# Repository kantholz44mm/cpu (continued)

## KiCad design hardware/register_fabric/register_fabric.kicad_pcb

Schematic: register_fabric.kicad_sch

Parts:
C2, C3, C5, C6, C8, C9, C11, C12, C14, C15, C17, C18, C20, C21, C23, C24, C25, C26, C27, C28, C29, C30, C31, C32, C33, C34, C35, C36: 330nF; C_0402_1005Metric; LCSC C77020
C4, C7, C10, C13, C16, C19, C22: 22uF; C_Radial_D5.0mm_H11.0mm_P2.00mm; not fitted
D141, D142, D143, D144, D145, D146, D147, D148, D149, D150, D151, D152, D153, D154, D155, D156, D157, D158, D159, D160, D161, D162, D163, D164, D165, D166, D167, D168, D169, D170, D171, D172, D173, D174, D175, D176, D177, D178, D179, D180, D181, D182, D183, D184, D185, D186, D187, D188, D189, D190, D191, D192, D193, D194, D195, D196, D197, D198, D199, D200, D201, D202: LED; LED_0402_1005Metric; LCSC C965793
H1, H2, H3, H4, H5, H6, H7, H8: MountingHole_Pad; MountingHole_3.2mm_M3_ISO7380_Pad_TopBottom
J2: Conn_02x40_Odd_Even; PinSocket_2x40_P2.54mm_Horizontal; not fitted
J3, J4, J5, J6, J7, J8, J9: Conn_02x16_Odd_Even; PinSocket_2x16_P2.54mm_Horizontal; not fitted
Q109, Q111, Q113, Q115, Q117, Q119, Q121, Q123, Q125, Q127, Q129, Q131, Q133, Q135, Q137, Q139, Q141, Q143, Q145, Q147, Q149, Q151, Q153, Q155, Q157, Q159, Q161, Q163, Q165, Q167, Q169, Q171, Q173, Q175, Q177, Q179, Q181, Q183, Q185, Q187, Q189, Q191, Q193, Q195, Q197, Q199, Q201, Q203, Q205, Q207, Q209, Q211, Q213, Q215, Q217, Q219, Q221, Q223, Q225, Q227, Q229: IRLML6244; SOT-23; LCSC C5123965
Q110, Q112, Q114, Q116, Q118, Q120, Q122, Q124, Q126, Q128, Q130, Q132, Q134, Q136, Q138, Q140, Q142, Q144, Q146, Q148, Q150, Q152, Q154, Q156, Q158, Q160, Q162, Q164, Q166, Q168, Q170, Q172, Q174, Q176, Q178, Q180, Q182, Q184, Q186, Q188, Q190, Q192, Q194, Q196, Q198, Q200, Q202, Q204, Q206, Q208, Q210, Q212, Q214, Q216, Q218, Q220, Q222, Q224, Q226, Q228, Q230: IRLML6402; SOT-23; LCSC C2886430
R1, R2, R3, R4, R5, R6, R7, R8, R9, R10, R11, R12, R13, R14, R15, R16, R21, R22, R23, R24, R25, R26, R27, R28, R29, R30, R31, R32, R33, R34, R35, R36, R37, R38, R39, R40, R41, R45, R46, R47, R48, R49, R50, R51, R52: 100K; R_0402_1005Metric; LCSC C60491
R122, R123, R124, R125, R126, R127, R128, R129, R130, R131, R132, R133, R134, R135, R136, R137, R138, R139, R140, R141, R142, R143, R144, R145, R146, R147, R148, R149, R150, R151, R152, R153, R154, R155, R156, R157, R158, R159, R160, R161, R162, R163, R164, R165, R166, R167, R168, R169, R170, R171, R172, R173, R174, R175, R176, R177, R178, R179, R180, R181, R182, R183, R184, R185, R186, R187, R188, R189, R190, R191, R192, R193, R194, R195, R196, R197, R198, R199, R200, R201, R202, R203, R204, R205, R206, R207, R208, R209, R210, R211, R212, R213, R214, R215, R216, R217, R218, R219, R220, R221, R222, R223, R224, R225, R226, R227, R228, R229, R230, R231, R232, R233, R234, R235, R236, R237, R238, R239, R240, R241, R242, R243, R244: 1000; R_0402_1005Metric; LCSC C106235
U1, U3, U4, U5, U6, U7, U8, U9, U10, U11, U12, U13, U14, U15, U16, U17: 74HC245; TSSOP-20_4.4x6.5mm_P0.65mm; LCSC C5626
U2, U18: 74HC138; SOIC-16_3.9x9.9mm_P1.27mm; LCSC C5602
U19, U21, U22, U23, U24, U25, U26: 74HC00; SOIC-14_3.9x8.7mm_P1.27mm; LCSC C5586
U20: 74HC238; SOIC-16_3.9x9.9mm_P1.27mm; LCSC C5620
U89, U90: 74LS157; SOIC-16_3.9x9.9mm_P1.27mm; LCSC C6823

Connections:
+5V: C2.1, C3.1, C4.1, C5.1, C6.1, C7.1, C8.1, C9.1, C10.1, C11.1, C12.1, C13.1, C14.1, C15.1, C16.1, C17.1, C18.1, C19.1, C20.1, C21.1, C22.1, C23.1, C24.1, C25.1, C26.1, C27.1, C28.1, C29.1, C30.1, C31.1, C32.1, C33.1, C34.1, C35.1, C36.1, D202.2 (A), J2.71, J2.73, J2.75, J2.77, J3.24, J3.26, J3.28, J3.30, J4.24, J4.26, J4.28, J4.30, J5.24, J5.26, J5.28, J5.30, J6.24, J6.26, J6.28, J6.30, J7.24, J7.26, J7.28, J7.30, J8.24, J8.26, J8.28, J8.30, J9.24, J9.26, J9.28, J9.30, Q110.2 (S), Q112.2 (S), Q114.2 (S), Q116.2 (S), Q118.2 (S), Q120.2 (S), Q122.2 (S), Q124.2 (S), Q126.2 (S), Q128.2 (S), Q130.2 (S), Q132.2 (S), Q134.2 (S), Q136.2 (S), Q138.2 (S), Q140.2 (S), Q142.2 (S), Q144.2 (S), Q146.2 (S), Q148.2 (S), Q150.2 (S), Q152.2 (S), Q154.2 (S), Q156.2 (S), Q158.2 (S), Q160.2 (S), Q162.2 (S), Q164.2 (S), Q166.2 (S), Q168.2 (S), Q170.2 (S), Q172.2 (S), Q174.2 (S), Q176.2 (S), Q178.2 (S), Q180.2 (S), Q182.2 (S), Q184.2 (S), Q186.2 (S), Q188.2 (S), Q190.2 (S), Q192.2 (S), Q194.2 (S), Q196.2 (S), Q198.2 (S), Q200.2 (S), Q202.2 (S), Q204.2 (S), Q206.2 (S), Q208.2 (S), Q210.2 (S), Q212.2 (S), Q214.2 (S), Q216.2 (S), Q218.2 (S), Q220.2 (S), Q222.2 (S), Q224.2 (S), Q226.2 (S), Q228.2 (S), Q230.2 (S), R1.1, R2.1, R3.1, R4.1, R5.1, R6.1, R7.1, R8.1, R9.1, R10.1, R11.1, R12.1, R13.1, R14.1, R15.1, R16.1, R122.2, R123.2, R124.2, R125.2, R126.2, R127.2, R128.2, R129.2, R130.2, R131.2, R132.2, R133.2, R134.2, R135.2, R136.2, R137.2, R138.2, R139.2, R140.2, R141.2, R142.2, R143.2, R144.2, R145.2, R146.2, R147.2, R148.2, R149.2, R150.2, R151.2, R152.2, R153.2, R154.2, R155.2, R156.2, R157.2, R158.2, R159.2, R160.2, R161.2, R162.2, R163.2, R164.2, R208.2, R210.2, R212.2, R214.2, R216.2, R218.2, R220.2, R222.2, R224.2, R226.2, R228.2, R230.2, R232.2, R234.2, R236.2, R238.2, R240.2, R242.2, U1.1 (A->B), U1.20 (VCC), U2.6 (E2), U2.16 (VCC), U3.1 (A->B), U3.20 (VCC), U4.1 (A->B), U4.20 (VCC), U5.1 (A->B), U5.20 (VCC), U6.1 (A->B), U6.20 (VCC), U7.1 (A->B), U7.20 (VCC), U8.1 (A->B), U8.20 (VCC), U9.1 (A->B), U9.20 (VCC), U10.1 (A->B), U10.20 (VCC), U11.1 (A->B), U11.20 (VCC), U12.1 (A->B), U12.20 (VCC), U13.1 (A->B), U13.20 (VCC), U14.1 (A->B), U14.20 (VCC), U15.1 (A->B), U15.20 (VCC), U16.1 (A->B), U16.20 (VCC), U17.1 (A->B), U17.20 (VCC), U18.6 (E2), U18.16 (VCC), U19.14 (VCC), U20.6 (E3), U20.16 (VCC), U21.14 (VCC), U22.14 (VCC), U23.14 (VCC), U24.14 (VCC), U25.14 (VCC), U26.14 (VCC), U89.16 (VCC), U90.16 (VCC)
/!CLR: J2.65, Q229.1 (G), R41.1
/CLK: J2.67, Q227.1 (G), R40.1
/COUT: J2.74, J7.5, U12.4 (A2), U13.4 (A2)
/DI0: J2.3, Q123.1 (G), R28.1
/DI1: J2.5, Q121.1 (G), R27.1
/DI2: J2.7, Q119.1 (G), R26.1
/DI3: J2.9, Q117.1 (G), R25.1
/DI4: J2.11, Q115.1 (G), R24.1
/DI5: J2.13, Q113.1 (G), R23.1
/DI6: J2.15, Q111.1 (G), R22.1
/DI7: J2.17, Q109.1 (G), R21.1
/DII0: D148.2 (A), J3.13, J4.13, J5.13, J6.13, J8.13, J9.13, Q124.3 (D), U89.2 (I0a)
/DII1: D147.2 (A), J3.14, J4.14, J5.14, J6.14, J8.14, J9.14, Q122.3 (D), U89.5 (I0b)
/DII2: D146.2 (A), J3.15, J4.15, J5.15, J6.15, J8.15, J9.15, Q120.3 (D), U89.11 (I0c)
/DII3: D145.2 (A), J3.16, J4.16, J5.16, J6.16, J8.16, J9.16, Q118.3 (D), U89.14 (I0d)
/DII4: D144.2 (A), J3.17, J4.17, J5.17, J6.17, J8.17, J9.17, Q116.3 (D), U90.2 (I0a)
/DII5: D143.2 (A), J3.18, J4.18, J5.18, J6.18, J8.18, J9.18, Q114.3 (D), U90.5 (I0b)
/DII6: D142.2 (A), J3.19, J4.19, J5.19, J6.19, J8.19, J9.19, Q112.3 (D), U90.11 (I0c)
/DII7: D141.2 (A), J3.20, J4.20, J5.20, J6.20, J8.20, J9.20, Q110.3 (D), U90.14 (I0d)
/FI0: J2.4, Q171.1 (G), R52.1
/FI1: J2.6, Q169.1 (G), R51.1
/FI2: J2.8, Q167.1 (G), R50.1
/FI3: J2.10, Q165.1 (G), R49.1
/FI4: J2.12, Q163.1 (G), R48.1
/FI5: J2.14, Q161.1 (G), R47.1
/FI6: J2.16, Q159.1 (G), R46.1
/FI7: J2.18, Q157.1 (G), R45.1
/FII0: D172.2 (A), Q172.3 (D), U89.3 (I1a)
/FII1: D171.2 (A), Q170.3 (D), U89.6 (I1b)
/FII2: D170.2 (A), Q168.3 (D), U89.10 (I1c)
/FII3: D169.2 (A), Q166.3 (D), U89.13 (I1d)
/FII4: D168.2 (A), Q164.3 (D), U90.3 (I1a)
/FII5: D167.2 (A), Q162.3 (D), U90.6 (I1b)
/FII6: D166.2 (A), Q160.3 (D), U90.10 (I1c)
/FII7: D165.2 (A), Q158.3 (D), U90.13 (I1d)
/FWEN: J2.78, Q225.1 (G), R39.1
/I!CLR: D201.2 (A), J3.29, J4.29, J5.29, J6.29, J7.29, J8.29, J9.29, Q230.3 (D)
/ICLK: D200.2 (A), J3.25, J4.25, J5.25, J6.25, J7.25, J8.25, J9.25, Q228.3 (D)
/IFWEN: D199.2 (A), Q226.3 (D), U24.9, U24.10, U89.1 (S), U90.1 (S)
/IRWEN: D198.2 (A), Q224.3 (D), U19.1, U21.1, U22.1, U23.1, U24.1, U25.1, U26.1
/R00: D156.2 (A), J2.21, Q140.3 (D)
/R01: D155.2 (A), J2.23, Q138.3 (D)
/R02: D154.2 (A), J2.25, Q136.3 (D)
/R03: D153.2 (A), J2.27, Q134.3 (D)
/R04: D152.2 (A), J2.29, Q132.3 (D)
/R05: D151.2 (A), J2.31, Q130.3 (D)
/R06: D150.2 (A), J2.33, Q128.3 (D)
/R07: D149.2 (A), J2.35, Q126.3 (D)
/R10: D164.2 (A), J2.22, Q156.3 (D)
/R11: D163.2 (A), J2.24, Q154.3 (D)
/R12: D162.2 (A), J2.26, Q152.3 (D)
/R13: D161.2 (A), J2.28, Q150.3 (D)
/R14: D160.2 (A), J2.30, Q148.3 (D)
/R15: D159.2 (A), J2.32, Q146.3 (D)
/R16: D158.2 (A), J2.34, Q144.3 (D)
/R17: D157.2 (A), J2.36, Q142.3 (D)
/RA0: D188.2 (A), J2.39, Q204.3 (D)
/RA1: D187.2 (A), J2.41, Q202.3 (D)
/RA2: D186.2 (A), J2.43, Q200.3 (D)
/RA3: D185.2 (A), J2.45, Q198.3 (D)
/RA4: D184.2 (A), J2.47, Q196.3 (D)
/RA5: D183.2 (A), J2.49, Q194.3 (D)
/RA6: D182.2 (A), J2.51, Q192.3 (D)
/RA7: D181.2 (A), J2.53, Q190.3 (D)
/RA8: D180.2 (A), J2.40, Q188.3 (D)
/RA9: D179.2 (A), J2.42, Q186.3 (D)
/RA10: D178.2 (A), J2.44, Q184.3 (D)
/RA11: D177.2 (A), J2.46, Q182.3 (D)
/RA12: D176.2 (A), J2.48, Q180.3 (D)
/RA13: D175.2 (A), J2.50, Q178.3 (D)
/RA14: D174.2 (A), J2.52, Q176.3 (D)
/RA15: D173.2 (A), J2.54, Q174.3 (D)
/RAI0: J8.3, Q203.1 (G), U14.2 (A0), U15.2 (A0)
/RAI1: J8.4, Q201.1 (G), U14.3 (A1), U15.3 (A1)
/RAI2: J8.5, Q199.1 (G), U14.4 (A2), U15.4 (A2)
/RAI3: J8.6, Q197.1 (G), U14.5 (A3), U15.5 (A3)
/RAI4: J8.7, Q195.1 (G), U14.6 (A4), U15.6 (A4)
/RAI5: J8.8, Q193.1 (G), U14.7 (A5), U15.7 (A5)
/RAI6: J8.9, Q191.1 (G), U14.8 (A6), U15.8 (A6)
/RAI7: J8.10, Q189.1 (G), U14.9 (A7), U15.9 (A7)
/RAI8: J9.3, Q187.1 (G), U16.2 (A0), U17.2 (A0)
/RAI9: J9.4, Q185.1 (G), U16.3 (A1), U17.3 (A1)
/RAI10: J9.5, Q183.1 (G), U16.4 (A2), U17.4 (A2)
/RAI11: J9.6, Q181.1 (G), U16.5 (A3), U17.5 (A3)
/RAI12: J9.7, Q179.1 (G), U16.6 (A4), U17.6 (A4)
/RAI13: J9.8, Q177.1 (G), U16.7 (A5), U17.7 (A5)
/RAI14: J9.9, Q175.1 (G), U16.8 (A6), U17.8 (A6)
/RAI15: J9.10, Q173.1 (G), U16.9 (A7), U17.9 (A7)
/RI00: Q139.1 (G), U1.18 (B0), U4.18 (B0), U6.18 (B0), U8.18 (B0), U10.18 (B0), U12.18 (B0), U14.18 (B0), U16.18 (B0)
/RI01: Q137.1 (G), U1.17 (B1), U4.17 (B1), U6.17 (B1), U8.17 (B1), U10.17 (B1), U12.17 (B1), U14.17 (B1), U16.17 (B1)
/RI02: Q135.1 (G), U1.16 (B2), U4.16 (B2), U6.16 (B2), U8.16 (B2), U10.16 (B2), U12.16 (B2), U14.16 (B2), U16.16 (B2)
/RI03: Q133.1 (G), U1.15 (B3), U4.15 (B3), U6.15 (B3), U8.15 (B3), U10.15 (B3), U12.15 (B3), U14.15 (B3), U16.15 (B3)
/RI04: Q131.1 (G), U1.14 (B4), U4.14 (B4), U6.14 (B4), U8.14 (B4), U10.14 (B4), U12.14 (B4), U14.14 (B4), U16.14 (B4)
/RI05: Q129.1 (G), U1.13 (B5), U4.13 (B5), U6.13 (B5), U8.13 (B5), U10.13 (B5), U12.13 (B5), U14.13 (B5), U16.13 (B5)
/RI06: Q127.1 (G), U1.12 (B6), U4.12 (B6), U6.12 (B6), U8.12 (B6), U10.12 (B6), U12.12 (B6), U14.12 (B6), U16.12 (B6)
/RI07: Q125.1 (G), U1.11 (B7), U4.11 (B7), U6.11 (B7), U8.11 (B7), U10.11 (B7), U12.11 (B7), U14.11 (B7), U16.11 (B7)
/RI10: Q155.1 (G), U3.18 (B0), U5.18 (B0), U7.18 (B0), U9.18 (B0), U11.18 (B0), U13.18 (B0), U15.18 (B0), U17.18 (B0)
/RI11: Q153.1 (G), U3.17 (B1), U5.17 (B1), U7.17 (B1), U9.17 (B1), U11.17 (B1), U13.17 (B1), U15.17 (B1), U17.17 (B1)
/RI12: Q151.1 (G), U3.16 (B2), U5.16 (B2), U7.16 (B2), U9.16 (B2), U11.16 (B2), U13.16 (B2), U15.16 (B2), U17.16 (B2)
/RI13: Q149.1 (G), U3.15 (B3), U5.15 (B3), U7.15 (B3), U9.15 (B3), U11.15 (B3), U13.15 (B3), U15.15 (B3), U17.15 (B3)
/RI14: Q147.1 (G), U3.14 (B4), U5.14 (B4), U7.14 (B4), U9.14 (B4), U11.14 (B4), U13.14 (B4), U15.14 (B4), U17.14 (B4)
/RI15: Q145.1 (G), U3.13 (B5), U5.13 (B5), U7.13 (B5), U9.13 (B5), U11.13 (B5), U13.13 (B5), U15.13 (B5), U17.13 (B5)
/RI16: Q143.1 (G), U3.12 (B6), U5.12 (B6), U7.12 (B6), U9.12 (B6), U11.12 (B6), U13.12 (B6), U15.12 (B6), U17.12 (B6)
/RI17: Q141.1 (G), U3.11 (B7), U5.11 (B7), U7.11 (B7), U9.11 (B7), U11.11 (B7), U13.11 (B7), U15.11 (B7), U17.11 (B7)
/RS00: J2.58, Q209.1 (G), R31.1
/RS01: J2.60, Q207.1 (G), R30.1
/RS02: J2.62, Q205.1 (G), R29.1
/RS10: J2.57, Q215.1 (G), R34.1
/RS11: J2.59, Q213.1 (G), R33.1
/RS12: J2.61, Q211.1 (G), R32.1
/RSI00: D191.2 (A), Q210.3 (D), U2.1 (A0)
/RSI01: D190.2 (A), Q208.3 (D), U2.2 (A1)
/RSI02: D189.2 (A), Q206.3 (D), U2.3 (A2)
/RSI10: D194.2 (A), Q216.3 (D), U18.1 (A0)
/RSI11: D193.2 (A), Q214.3 (D), U18.2 (A1)
/RSI12: D192.2 (A), Q212.3 (D), U18.3 (A2)
/RWEN: J2.76, Q223.1 (G), R38.1
/WS0: J2.66, Q221.1 (G), R37.1
/WS1: J2.68, Q219.1 (G), R36.1
/WS2: J2.70, Q217.1 (G), R35.1
/WSI0: D197.2 (A), Q222.3 (D), U20.1 (A0)
/WSI1: D196.2 (A), Q220.3 (D), U20.2 (A1)
/WSI2: D195.2 (A), Q218.3 (D), U20.3 (A2)
GND: C2.2, C3.2, C4.2, C5.2, C6.2, C7.2, C8.2, C9.2, C10.2, C11.2, C12.2, C13.2, C14.2, C15.2, C16.2, C17.2, C18.2, C19.2, C20.2, C21.2, C22.2, C23.2, C24.2, C25.2, C26.2, C27.2, C28.2, C29.2, C30.2, C31.2, C32.2, C33.2, C34.2, C35.2, C36.2, H1.1, H2.1, H3.1, H4.1, H5.1, H6.1, H7.1, H8.1, J2.1, J2.2, J2.19, J2.20, J2.37, J2.38, J2.55, J2.56, J2.63, J2.64, J2.69, J2.72, J2.79, J2.80, J3.1, J3.2, J3.11, J3.12, J3.21, J3.22, J3.23, J3.31, J3.32, J4.1, J4.2, J4.11, J4.12, J4.21, J4.22, J4.23, J4.31, J4.32, J5.1, J5.2, J5.11, J5.12, J5.21, J5.22, J5.23, J5.31, J5.32, J6.1, J6.2, J6.11, J6.12, J6.21, J6.22, J6.23, J6.31, J6.32, J7.1, J7.2, J7.11, J7.12, J7.21, J7.22, J7.23, J7.31, J7.32, J8.1, J8.2, J8.11, J8.12, J8.21, J8.22, J8.23, J8.31, J8.32, J9.1, J9.2, J9.11, J9.12, J9.21, J9.22, J9.23, J9.31, J9.32, Q109.2 (S), Q111.2 (S), Q113.2 (S), Q115.2 (S), Q117.2 (S), Q119.2 (S), Q121.2 (S), Q123.2 (S), Q125.2 (S), Q127.2 (S), Q129.2 (S), Q131.2 (S), Q133.2 (S), Q135.2 (S), Q137.2 (S), Q139.2 (S), Q141.2 (S), Q143.2 (S), Q145.2 (S), Q147.2 (S), Q149.2 (S), Q151.2 (S), Q153.2 (S), Q155.2 (S), Q157.2 (S), Q159.2 (S), Q161.2 (S), Q163.2 (S), Q165.2 (S), Q167.2 (S), Q169.2 (S), Q171.2 (S), Q173.2 (S), Q175.2 (S), Q177.2 (S), Q179.2 (S), Q181.2 (S), Q183.2 (S), Q185.2 (S), Q187.2 (S), Q189.2 (S), Q191.2 (S), Q193.2 (S), Q195.2 (S), Q197.2 (S), Q199.2 (S), Q201.2 (S), Q203.2 (S), Q205.2 (S), Q207.2 (S), Q209.2 (S), Q211.2 (S), Q213.2 (S), Q215.2 (S), Q217.2 (S), Q219.2 (S), Q221.2 (S), Q223.2 (S), Q225.2 (S), Q227.2 (S), Q229.2 (S), R21.2, R22.2, R23.2, R24.2, R25.2, R26.2, R27.2, R28.2, R29.2, R30.2, R31.2, R32.2, R33.2, R34.2, R35.2, R36.2, R37.2, R38.2, R39.2, R40.2, R41.2, R45.2, R46.2, R47.2, R48.2, R49.2, R50.2, R51.2, R52.2, R165.1, R166.1, R167.1, R168.1, R169.1, R170.1, R171.1, R172.1, R173.1, R174.1, R175.1, R176.1, R177.1, R178.1, R179.1, R180.1, R181.1, R182.1, R183.1, R184.1, R185.1, R186.1, R187.1, R188.1, R189.1, R190.1, R191.1, R192.1, R193.1, R194.1, R195.1, R196.1, R197.1, R198.1, R199.1, R200.1, R201.1, R202.1, R203.1, R204.1, R205.1, R206.1, R207.1, R209.1, R211.1, R213.1, R215.1, R217.1, R219.1, R221.1, R223.1, R225.1, R227.1, R229.1, R231.1, R233.1, R235.1, R237.1, R239.1, R241.1, R243.1, R244.1, U1.2 (A0), U1.3 (A1), U1.4 (A2), U1.5 (A3), U1.6 (A4), U1.7 (A5), U1.8 (A6), U1.9 (A7), U1.10 (GND), U2.4 (~E0), U2.5 (~E1), U2.8 (GND), U3.2 (A0), U3.3 (A1), U3.4 (A2), U3.5 (A3), U3.6 (A4), U3.7 (A5), U3.8 (A6), U3.9 (A7), U3.10 (GND), U4.10 (GND), U5.10 (GND), U6.10 (GND), U7.10 (GND), U8.10 (GND), U9.10 (GND), U10.10 (GND), U11.10 (GND), U12.10 (GND), U13.10 (GND), U14.10 (GND), U15.10 (GND), U16.10 (GND), U17.10 (GND), U18.4 (~E0), U18.5 (~E1), U18.8 (GND), U19.7 (GND), U19.9, U19.10, U19.12, U19.13, U20.4 (~E1), U20.5 (~E2), U20.8 (GND), U21.7 (GND), U21.9, U21.10, U21.12, U21.13, U22.7 (GND), U22.9, U22.10, U22.12, U22.13, U23.7 (GND), U23.9, U23.10, U23.12, U23.13, U24.7 (GND), U24.12, U24.13, U25.7 (GND), U25.9, U25.10, U25.12, U25.13, U26.7 (GND), U26.9, U26.10, U26.12, U26.13, U89.8 (GND), U89.15 (E), U90.8 (GND), U90.15 (E)
unnamed: D141.1 (K), R165.2
unnamed: D142.1 (K), R166.2
unnamed: D143.1 (K), R167.2
unnamed: D144.1 (K), R168.2
unnamed: D145.1 (K), R169.2
unnamed: D146.1 (K), R170.2
unnamed: D147.1 (K), R171.2
unnamed: D148.1 (K), R172.2
unnamed: D149.1 (K), R173.2
unnamed: D150.1 (K), R174.2
unnamed: D151.1 (K), R175.2
unnamed: D152.1 (K), R176.2
unnamed: D153.1 (K), R177.2
unnamed: D154.1 (K), R178.2
unnamed: D155.1 (K), R179.2
unnamed: D156.1 (K), R180.2
unnamed: D157.1 (K), R181.2
unnamed: D158.1 (K), R182.2
unnamed: D159.1 (K), R183.2
unnamed: D160.1 (K), R184.2
unnamed: D161.1 (K), R185.2
unnamed: D162.1 (K), R186.2
unnamed: D163.1 (K), R187.2
unnamed: D164.1 (K), R188.2
unnamed: D165.1 (K), R189.2
unnamed: D166.1 (K), R190.2
unnamed: D167.1 (K), R191.2
unnamed: D168.1 (K), R192.2
unnamed: D169.1 (K), R193.2
unnamed: D170.1 (K), R194.2
unnamed: D171.1 (K), R195.2
unnamed: D172.1 (K), R196.2
unnamed: D173.1 (K), R197.2
unnamed: D174.1 (K), R198.2
unnamed: D175.1 (K), R199.2
unnamed: D176.1 (K), R200.2
unnamed: D177.1 (K), R201.2
unnamed: D178.1 (K), R202.2
unnamed: D179.1 (K), R203.2
unnamed: D180.1 (K), R204.2
unnamed: D181.1 (K), R205.2
unnamed: D182.1 (K), R206.2
unnamed: D183.1 (K), R207.2
unnamed: D184.1 (K), R209.2
unnamed: D185.1 (K), R211.2
unnamed: D186.1 (K), R213.2
unnamed: D187.1 (K), R215.2
unnamed: D188.1 (K), R217.2
unnamed: D189.1 (K), R219.2
unnamed: D190.1 (K), R221.2
unnamed: D191.1 (K), R223.2
unnamed: D192.1 (K), R225.2
unnamed: D193.1 (K), R227.2
unnamed: D194.1 (K), R229.2
unnamed: D195.1 (K), R231.2
unnamed: D196.1 (K), R233.2
unnamed: D197.1 (K), R235.2
unnamed: D198.1 (K), R237.2
unnamed: D199.1 (K), R239.2
unnamed: D200.1 (K), R241.2
unnamed: D201.1 (K), R243.2
unnamed: D202.1 (K), R244.2
unnamed: J3.3, U4.2 (A0), U5.2 (A0)
unnamed: J3.4, U4.3 (A1), U5.3 (A1)
unnamed: J3.5, U4.4 (A2), U5.4 (A2)
unnamed: J3.6, U4.5 (A3), U5.5 (A3)
unnamed: J3.7, U4.6 (A4), U5.6 (A4)
unnamed: J3.8, U4.7 (A5), U5.7 (A5)
unnamed: J3.9, U4.8 (A6), U5.8 (A6)
unnamed: J3.10, U4.9 (A7), U5.9 (A7)
unnamed: J3.27, U19.6
unnamed: J4.3, U6.2 (A0), U7.2 (A0)
unnamed: J4.4, U6.3 (A1), U7.3 (A1)
unnamed: J4.5, U6.4 (A2), U7.4 (A2)
unnamed: J4.6, U6.5 (A3), U7.5 (A3)
unnamed: J4.7, U6.6 (A4), U7.6 (A4)
unnamed: J4.8, U6.7 (A5), U7.7 (A5)
unnamed: J4.9, U6.8 (A6), U7.8 (A6)
unnamed: J4.10, U6.9 (A7), U7.9 (A7)
unnamed: J4.27, U21.6
unnamed: J5.3, U8.2 (A0), U9.2 (A0)
unnamed: J5.4, U8.3 (A1), U9.3 (A1)
unnamed: J5.5, U8.4 (A2), U9.4 (A2)
unnamed: J5.6, U8.5 (A3), U9.5 (A3)
unnamed: J5.7, U8.6 (A4), U9.6 (A4)
unnamed: J5.8, U8.7 (A5), U9.7 (A5)
unnamed: J5.9, U8.8 (A6), U9.8 (A6)
unnamed: J5.10, U8.9 (A7), U9.9 (A7)
unnamed: J5.27, U22.6
unnamed: J6.3, U10.2 (A0), U11.2 (A0)
unnamed: J6.4, U10.3 (A1), U11.3 (A1)
unnamed: J6.5, U10.4 (A2), U11.4 (A2)
unnamed: J6.6, U10.5 (A3), U11.5 (A3)
unnamed: J6.7, U10.6 (A4), U11.6 (A4)
unnamed: J6.8, U10.7 (A5), U11.7 (A5)
unnamed: J6.9, U10.8 (A6), U11.8 (A6)
unnamed: J6.10, U10.9 (A7), U11.9 (A7)
unnamed: J6.27, U23.6
unnamed: J7.3, U12.2 (A0), U13.2 (A0)
unnamed: J7.4, U12.3 (A1), U13.3 (A1)
unnamed: J7.6, U12.5 (A3), U13.5 (A3)
unnamed: J7.7, U12.6 (A4), U13.6 (A4)
unnamed: J7.8, U12.7 (A5), U13.7 (A5)
unnamed: J7.9, U12.8 (A6), U13.8 (A6)
unnamed: J7.10, U12.9 (A7), U13.9 (A7)
unnamed: J7.13, U89.4 (Za)
unnamed: J7.14, U89.7 (Zb)
unnamed: J7.15, U89.9 (Zc)
unnamed: J7.16, U89.12 (Zd)
unnamed: J7.17, U90.4 (Za)
unnamed: J7.18, U90.7 (Zb)
unnamed: J7.19, U90.9 (Zc)
unnamed: J7.20, U90.12 (Zd)
unnamed: J7.27, U24.6
unnamed: J8.27, U25.6
unnamed: J9.27, U26.6
unnamed: Q109.3 (D), Q110.1 (G), R122.1
unnamed: Q111.3 (D), Q112.1 (G), R123.1
unnamed: Q113.3 (D), Q114.1 (G), R124.1
unnamed: Q115.3 (D), Q116.1 (G), R125.1
unnamed: Q117.3 (D), Q118.1 (G), R126.1
unnamed: Q119.3 (D), Q120.1 (G), R127.1
unnamed: Q121.3 (D), Q122.1 (G), R128.1
unnamed: Q123.3 (D), Q124.1 (G), R129.1
unnamed: Q125.3 (D), Q126.1 (G), R130.1
unnamed: Q127.3 (D), Q128.1 (G), R131.1
unnamed: Q129.3 (D), Q130.1 (G), R132.1
unnamed: Q131.3 (D), Q132.1 (G), R133.1
unnamed: Q133.3 (D), Q134.1 (G), R134.1
unnamed: Q135.3 (D), Q136.1 (G), R135.1
unnamed: Q137.3 (D), Q138.1 (G), R136.1
unnamed: Q139.3 (D), Q140.1 (G), R137.1
unnamed: Q141.3 (D), Q142.1 (G), R138.1
unnamed: Q143.3 (D), Q144.1 (G), R139.1
unnamed: Q145.3 (D), Q146.1 (G), R140.1
unnamed: Q147.3 (D), Q148.1 (G), R141.1
unnamed: Q149.3 (D), Q150.1 (G), R142.1
unnamed: Q151.3 (D), Q152.1 (G), R143.1
unnamed: Q153.3 (D), Q154.1 (G), R144.1
unnamed: Q155.3 (D), Q156.1 (G), R145.1
unnamed: Q157.3 (D), Q158.1 (G), R146.1
unnamed: Q159.3 (D), Q160.1 (G), R147.1
unnamed: Q161.3 (D), Q162.1 (G), R148.1
unnamed: Q163.3 (D), Q164.1 (G), R149.1
unnamed: Q165.3 (D), Q166.1 (G), R150.1
unnamed: Q167.3 (D), Q168.1 (G), R151.1
unnamed: Q169.3 (D), Q170.1 (G), R152.1
unnamed: Q171.3 (D), Q172.1 (G), R153.1
unnamed: Q173.3 (D), Q174.1 (G), R154.1
unnamed: Q175.3 (D), Q176.1 (G), R155.1
unnamed: Q177.3 (D), Q178.1 (G), R156.1
unnamed: Q179.3 (D), Q180.1 (G), R157.1
unnamed: Q181.3 (D), Q182.1 (G), R158.1
unnamed: Q183.3 (D), Q184.1 (G), R159.1
unnamed: Q185.3 (D), Q186.1 (G), R160.1
unnamed: Q187.3 (D), Q188.1 (G), R161.1
unnamed: Q189.3 (D), Q190.1 (G), R162.1
unnamed: Q191.3 (D), Q192.1 (G), R163.1
unnamed: Q193.3 (D), Q194.1 (G), R164.1
unnamed: Q195.3 (D), Q196.1 (G), R208.1
unnamed: Q197.3 (D), Q198.1 (G), R210.1
unnamed: Q199.3 (D), Q200.1 (G), R212.1
unnamed: Q201.3 (D), Q202.1 (G), R214.1
unnamed: Q203.3 (D), Q204.1 (G), R216.1
unnamed: Q205.3 (D), Q206.1 (G), R218.1
unnamed: Q207.3 (D), Q208.1 (G), R220.1
unnamed: Q209.3 (D), Q210.1 (G), R222.1
unnamed: Q211.3 (D), Q212.1 (G), R224.1
unnamed: Q213.3 (D), Q214.1 (G), R226.1
unnamed: Q215.3 (D), Q216.1 (G), R228.1
unnamed: Q217.3 (D), Q218.1 (G), R230.1
unnamed: Q219.3 (D), Q220.1 (G), R232.1
unnamed: Q221.3 (D), Q222.1 (G), R234.1
unnamed: Q223.3 (D), Q224.1 (G), R236.1
unnamed: Q225.3 (D), Q226.1 (G), R238.1
unnamed: Q227.3 (D), Q228.1 (G), R240.1
unnamed: Q229.3 (D), Q230.1 (G), R242.1
unnamed: R1.2, U1.19 (CE), U2.15 (~Y0)
unnamed: R3.2, U2.14 (~Y1), U4.19 (CE)
unnamed: R5.2, U2.13 (~Y2), U6.19 (CE)
unnamed: R7.2, U2.12 (~Y3), U8.19 (CE)
unnamed: R9.2, U2.11 (~Y4), U10.19 (CE)
unnamed: R10.2, U11.19 (CE), U18.11 (~Y4)
unnamed: R11.2, U2.10 (~Y5), U12.19 (CE)
unnamed: R12.2, U13.19 (CE), U18.10 (~Y5)
unnamed: R13.2, U2.9 (~Y6), U14.19 (CE)
unnamed: R14.2, U15.19 (CE), U18.9 (~Y6)
unnamed: R15.2, U2.7 (~Y7), U16.19 (CE)
unnamed: R16.2, U17.19 (CE), U18.7 (~Y7)
unnamed: R2.2, U3.19 (CE), U18.15 (~Y0)
unnamed: R4.2, U5.19 (CE), U18.14 (~Y1)
unnamed: R6.2, U7.19 (CE), U18.13 (~Y2)
unnamed: R8.2, U9.19 (CE), U18.12 (~Y3)
unnamed: U19.3, U19.4, U19.5
unnamed: U19.2, U20.14 (Y1)
unnamed: U20.13 (Y2), U21.2
unnamed: U20.12 (Y3), U22.2
unnamed: U20.11 (Y4), U23.2
unnamed: U20.10 (Y5), U24.2
unnamed: U20.9 (Y6), U25.2
unnamed: U20.7 (Y7), U26.2
unnamed: U21.3, U21.4, U21.5
unnamed: U22.3, U22.4, U22.5
unnamed: U23.3, U23.4, U23.5
unnamed: U24.3, U24.4
unnamed: U24.5, U24.8
unnamed: U25.3, U25.4, U25.5
unnamed: U26.3, U26.4, U26.5

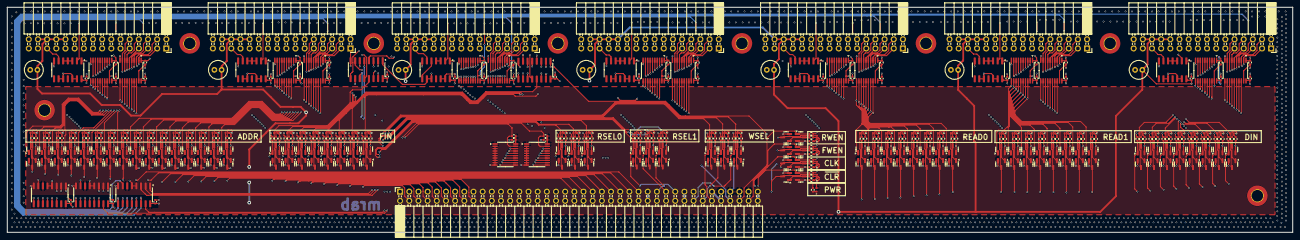
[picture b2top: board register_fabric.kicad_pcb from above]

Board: 4 copper layers, 356.0 x 62.3 mm, 431 parts (0 on the bottom side), 333 nets.

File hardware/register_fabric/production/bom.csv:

Designator,Footprint,Quantity,Value,LCSC Part #
"C11, C12, C14, C15, C17, C18, C2, C20, C21, C23, C24, C25, C26, C27, C28, C29, C3, C30, C31, C32, C33, C34, C35, C36, C5, C6, C8, C9",0402,28,330nF,C77020
"D141, D142, D143, D144, D145, D146, D147, D148, D149, D150, D151, D152, D153, D154, D155, D156, D157, D158, D159, D160, D161, D162, D163, D164, D165, D166, D167, D168, D169, D170, D171, D172, D173, D174, D175, D176, D177, D178, D179, D180, D181, D182, D183, D184, D185, D186, D187, D188, D189, D190, D191, D192, D193, D194, D195, D196, D197, D198, D199, D200, D201, D202",0402,62,LED,C965793
"Q109, Q111, Q113, Q115, Q117, Q119, Q121, Q123, Q125, Q127, Q129, Q131, Q133, Q135, Q137, Q139, Q141, Q143, Q145, Q147, Q149, Q151, Q153, Q155, Q157, Q159, Q161, Q163, Q165, Q167, Q169, Q171, Q173, Q175, Q177, Q179, Q181, Q183, Q185, Q187, Q189, Q191, Q193, Q195, Q197, Q199, Q201, Q203, Q205, Q207, Q209, Q211, Q213, Q215, Q217, Q219, Q221, Q223, Q225, Q227, Q229",SOT-23,61,IRLML6244,C5123965
"Q110, Q112, Q114, Q116, Q118, Q120, Q122, Q124, Q126, Q128, Q130, Q132, Q134, Q136, Q138, Q140, Q142, Q144, Q146, Q148, Q150, Q152, Q154, Q156, Q158, Q160, Q162, Q164, Q166, Q168, Q170, Q172, Q174, Q176, Q178, Q180, Q182, Q184, Q186, Q188, Q190, Q192, Q194, Q196, Q198, Q200, Q202, Q204, Q206, Q208, Q210, Q212, Q214, Q216, Q218, Q220, Q222, Q224, Q226, Q228, Q230",SOT-23,61,IRLML6402,C2886430
"R1, R10, R11, R12, R13, R14, R15, R16, R2, R21, R22, R23, R24, R25, R26, R27, R28, R29, R3, R30, R31, R32, R33, R34, R35, R36, R37, R38, R39, R4, R40, R41, R45, R46, R47, R48, R49, R5, R50, R51, R52, R6, R7, R8, R9",0402,45,100K,C60491
"R122, R123, R124, R125, R126, R127, R128, R129, R130, R131, R132, R133, R134, R135, R136, R137, R138, R139, R140, R141, R142, R143, R144, R145, R146, R147, R148, R149, R150, R151, R152, R153, R154, R155, R156, R157, R158, R159, R160, R161, R162, R163, R164, R165, R166, R167, R168, R169, R170, R171, R172, R173, R174, R175, R176, R177, R178, R179, R180, R181, R182, R183, R184, R185, R186, R187, R188, R189, R190, R191, R192, R193, R194, R195, R196, R197, R198, R199, R200, R201, R202, R203, R204, R205, R206, R207, R208, R209, R210, R211, R212, R213, R214, R215, R216, R217, R218, R219, R220, R221, R222, R223, R224, R225, R226, R227, R228, R229, R230, R231, R232, R233, R234, R235, R236, R237, R238, R239, R240, R241, R242, R243, R244",0402,123,1000,C106235
"U1, U10, U11, U12, U13, U14, U15, U16, U17, U3, U4, U5, U6, U7, U8, U9",TSSOP-20_4.4x6.5mm_P0.65mm,16,74HC245,C5626
"U18, U2",SOIC-16_3.9x9.9mm_P1.27mm,2,74HC138,C5602
"U19, U21, U22, U23, U24, U25, U26",SOIC-14_3.9x8.7mm_P1.27mm,7,74HC00,C5586
U20,SOIC-16_3.9x9.9mm_P1.27mm,1,74HC238,C5620
"U89, U90",SOIC-16_3.9x9.9mm_P1.27mm,2,74LS157,C6823
